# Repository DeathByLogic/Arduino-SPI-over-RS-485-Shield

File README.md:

Arduino-SPI-over-RS-485-Shield
==============================

An Arduino shield that converts the SPI signals from the Arduino to RS-485 for communications over long distances. If the distance is long enough to where the delay caused by the wire and transceivers causes the SPI communications to get out of sync there is a second SPI channel that can act as an slave device and receive the data back from the delayed SPI. There is also an LCD display and 5 button D-Pad for a control interface.

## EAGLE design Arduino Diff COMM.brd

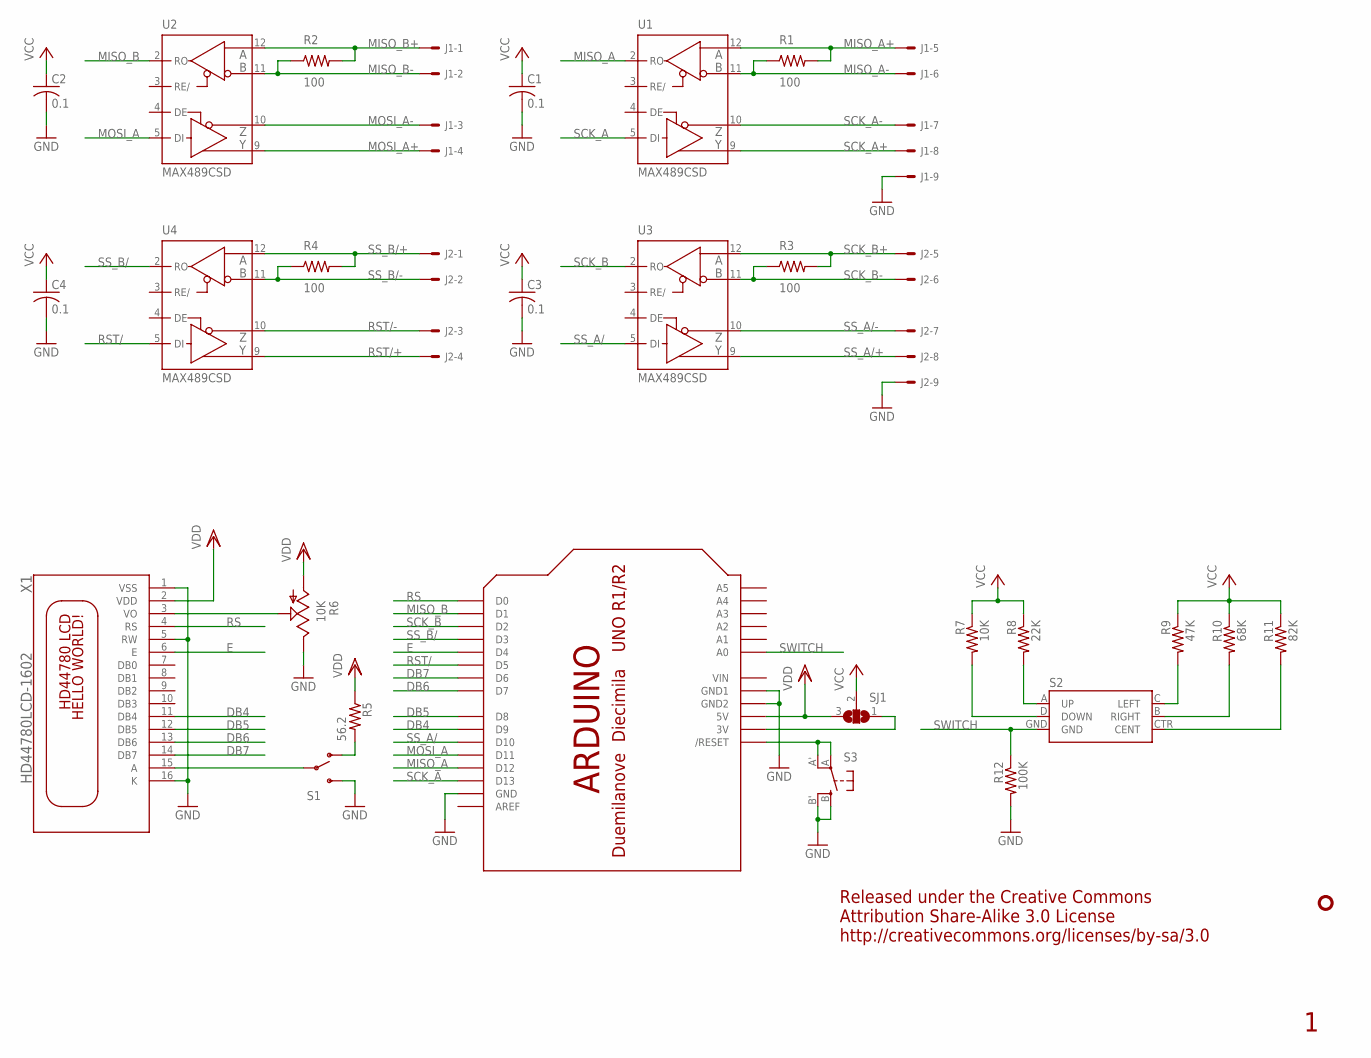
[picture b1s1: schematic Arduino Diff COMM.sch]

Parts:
C1, C2, C3, C4: 0.1; C0603K
J1, J2: 22-05-7098-09; 7395-09
R1, R2, R3, R4: 100; R1206
R5: 56.2; R0805
R6: 10K; 3223G
R7: 10K; R0805
R8: 22K; R0805
R9: 47K; R0805
R10: 68K; R0805
R11: 82K; R0805
R12: 100K; R0805
S1: SWITCH_SPDT; KPS-1290
S2: JOYSTICK_MINI
S3: SPST_TACT-EVQQ2; EVQ-Q2
SJ1: SJ2W; SJ_2
U1, U2, U3, U4: MAX489CSD; SO14
U$1: ARDUINO-NOHOLE
U$2: PENGUIN_LOGOCOPPER; PENGUIN_COPPER
X1: HD44780LCD-1602; LCD1602

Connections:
DB4: U$1.D9, X1.11 (DB4)
DB5: U$1.D8, X1.12 (DB5)
DB6: U$1.D7, X1.13 (DB6)
DB7: U$1.D6, X1.14 (DB7)
E: U$1.D4, X1.6 (E)
GND: C1.2, C2.2, C3.2, C4.2, J1.9, J2.9, R6.3 (E), R12.2, S1.S, S3.B (S), S3.B' (S1), U1.6 (GND), U1.7 (GND), U2.6 (GND), U2.7 (GND), U3.6 (GND), U3.7 (GND), U4.6 (GND), U4.7 (GND), U$1.GND, U$1.GND1, U$1.GND2, X1.1 (VSS), X1.5 (RW), X1.16 (K)
MISO_A: U1.2 (RO), U$1.D12
MISO_A+: J1.5, R1.2, U1.12 (A)
MISO_A-: J1.6, R1.1, U1.11 (B)
MISO_B: U2.2 (RO), U$1.D1
MISO_B+: J1.1, R2.2, U2.12 (A)
MISO_B-: J1.2, R2.1, U2.11 (B)
MOSI_A: U2.5 (DI), U$1.D11
MOSI_A+: J1.4, U2.9 (Y)
MOSI_A-: J1.3, U2.10 (Z)
unnamed: R5.2, S1.O
unnamed: R8.2, S2.A (UP)
unnamed: S1.P, X1.15 (A)
unnamed: R9.2, S2.C (LEFT)
unnamed: R11.2, S2.CTR (CENT)
unnamed: R10.2, S2.B (RIGHT)
unnamed: R7.2, S2.D (DOWN)
unnamed: R6.2 (S), X1.3 (VO)
unnamed: SJ1.1, U$1.3V
unnamed: S3.A, S3.A' (P1), U$1.RESET (/RESET)
RS: U$1.D0, X1.4 (RS)
RST/: U4.5 (DI), U$1.D5
RST/+: J2.4, U4.9 (Y)
RST/-: J2.3, U4.10 (Z)
SCK_A: U1.5 (DI), U$1.D13
SCK_A+: J1.8, U1.9 (Y)
SCK_A-: J1.7, U1.10 (Z)
SCK_B: U3.2 (RO), U$1.D2
SCK_B+: J2.5, R3.2, U3.12 (A)
SCK_B-: J2.6, R3.1, U3.11 (B)
SS_A/: U3.5 (DI), U$1.D10
SS_A/+: J2.8, U3.9 (Y)
SS_A/-: J2.7, U3.10 (Z)
SS_B/: U4.2 (RO), U$1.D3
SS_B/+: J2.1, R4.2, U4.12 (A)
SS_B/-: J2.2, R4.1, U4.11 (B)
SWITCH: R12.1, S2.GND, U$1.A0
VCC: C1.1, C2.1, C3.1, C4.1, R7.1, R8.1, R9.1, R10.1, R11.1, SJ1.2, U1.14 (VCC), U2.14 (VCC), U3.14 (VCC), U4.14 (VCC)
VDD: R5.1, R6.1 (A), SJ1.3, U$1.5V, X1.2 (VDD)
VIN: U$1.VIN

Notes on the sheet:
Released under the Creative Commons Attribution Share-Alike 3.0 License http://creativecommons.org/licenses/by-sa/3.0

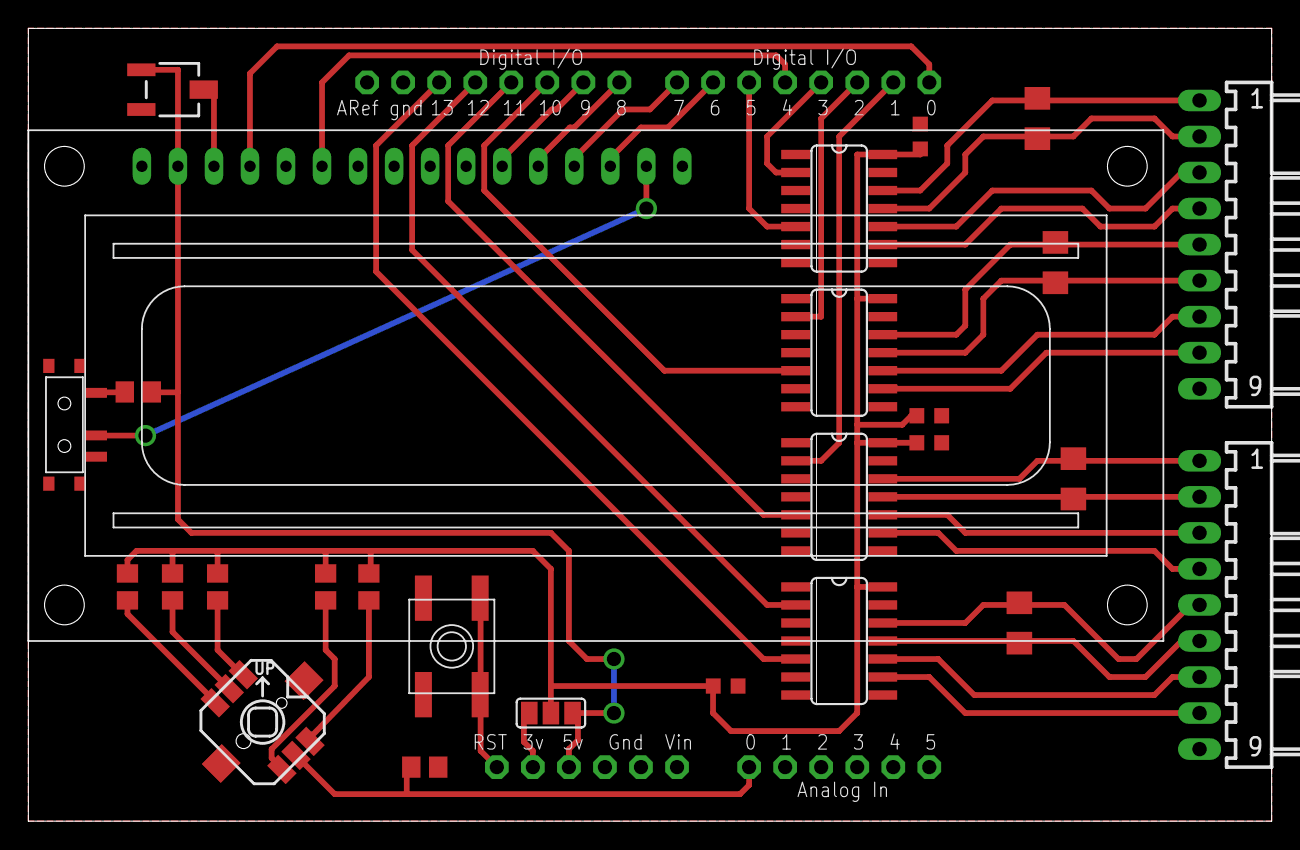
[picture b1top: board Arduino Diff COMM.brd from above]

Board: 2 copper layers, 87.6 x 55.9 mm, 29 parts (0 on the bottom side), 44 nets.

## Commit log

2014-09-14 Initial commit of version 1

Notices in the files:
Arduino Diff COMM.brd:
(C) 2014 D. Wassenberg
parts and their libraries:
SparkFun-Electromechanical: Licensing: CC v3.0 Share-Alike You are welcome to use this library for commercial purposes.
